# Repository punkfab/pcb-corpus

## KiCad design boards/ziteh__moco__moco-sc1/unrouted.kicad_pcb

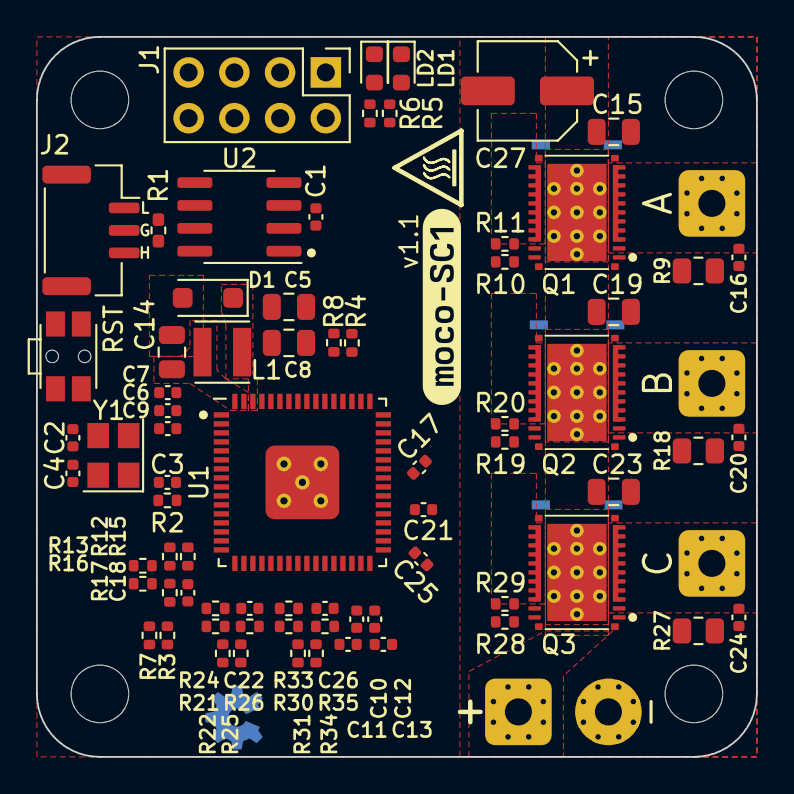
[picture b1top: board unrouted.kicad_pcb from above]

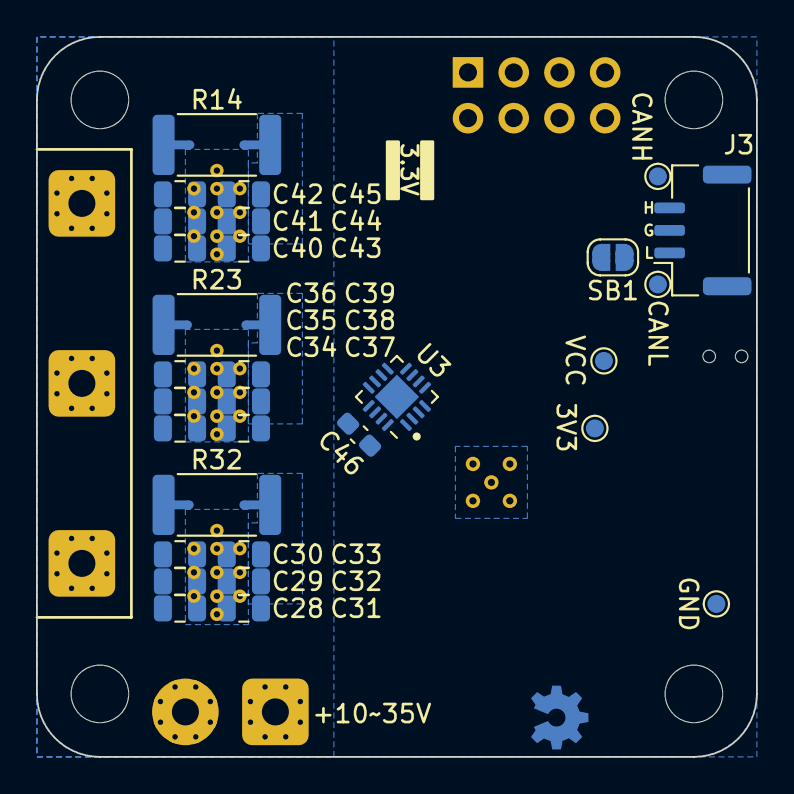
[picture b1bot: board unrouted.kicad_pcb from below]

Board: 4 copper layers, 40.0 x 40.0 mm, 118 parts (36 on the bottom side), 69 nets, no tracks yet.

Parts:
C1, C3, C6, C9, C10, C12: 100nF; C_0402_1005Metric
C2, C4: 6.8pF; C_0402_1005Metric
C5, C28, C29, C30, C31, C32, C33, C34, C35, C36, C37, C38, C39, C40, C41, C42, C43, C44, C45: 10uF/50V; C_0805_2012Metric
C7: 10uF; C_0402_1005Metric
C8, C15, C19, C23: 220nF/50V; C_0805_2012Metric
C11, C13: 1uF; C_0402_1005Metric
C14: 10uF; C_0805_2012Metric
C16, C20, C24: 4.7nF/50V; C_0402_1005Metric
C17, C21, C25: 100nF/50V; C_0402_1005Metric
C18, C22, C26: 1nF; C_0402_1005Metric
C27: 22uF/50V; CP_Elec_5x5.8
C46: 1uF; C_0603_1608Metric_Pad1.08x0.95mm_HandSolder
D1: MBR180S1; D_SOD-123F
H1, H2, H3, H4: MountingHole; MountingHole_3.2mm_M3_ISO14580
J1: Debug; PinHeader_2x04_P2.54mm_Vertical
J2, J3: CAN; JST_GH_SM03B-GHS-TB_1x03-1MP_P1.25mm_Horizontal
J4: V+; wire_rectagnel_3.7mm_D1.5mm
J5: V-; wire_circ_3.7mm_D1.5mm
J6: A; wire_rectagnel_3.7mm_D1.5mm
J7: B; wire_rectagnel_3.7mm_D1.5mm
J8: C; wire_rectagnel_3.7mm_D1.5mm
L1: 18uH; L_Neosid_SMS-ME3015
LD1: Red; LED_0603_1608Metric
LD2: Blue; LED_0603_1608Metric
NT1, NT2, NT3, NT4, NT5, NT6: NetTie_2; NetTie-2_SMD_Pad0.5mm
Q1, Q2, Q3: CSD88584Q5DC; VSON-CLIP-22_5x6mm (DMM0022A)_Alt1
R1: 120R; R_0402_1005Metric_Pad0.72x0.64mm_HandSolder
R2, R6, R7, R8: 10k; R_0402_1005Metric
R3: 100k; R_0402_1005Metric
R4: 22k; R_0402_1005Metric
R5: 1k; R_0402_1005Metric
R9, R18, R27: 2.2R/125mW; R_0805_2012Metric
R10, R11, R19, R20, R28, R29: 10R; R_0402_1005Metric
R12, R15, R21, R24, R30, R33: 24k; R_0402_1005Metric
R13, R16, R22, R25, R31, R34: 1.78k; R_0402_1005Metric
R14, R23, R32: 20mΩ/3W; R_2512_6332Metric
R17, R26, R35: 12k; R_0402_1005Metric
SB1: SolderJumper_2_Open; SolderJumper-2_P1.3mm_Open_RoundedPad1.0x1.5mm
SW1: RESET; SW_SPST_EVQP7C
TP1: CANH; TestPoint_Pad_D1.0mm
TP2: CANL; TestPoint_Pad_D1.0mm
TP3: 3.3V; TestPoint_Pad_D1.0mm
TP4: VCC; TestPoint_Pad_D1.0mm
TP5: GND; TestPoint_Pad_D1.0mm
U1: STSPIN32G4; VFQFPN 9X9X1.0 64 PITCH 0.5
U2: TCAN337; SOIC-8_3.9x4.9mm_P1.27mm
U3: MA702; QFN-16-1EP_3x3mm_P0.5mm_EP1.75x1.75mm
Y1: 16MHz; Crystal_SMD_3225-4Pin_3.2x2.5mm
kibuzzard-64C58EFF: G***; kibuzzard-64C58EFF

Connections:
+3.3V: C1.2, C6.2, C7.2, C9.2, C10.2, C11.2, C12.2, C13.2, C46.2, J1.1, R2.2, R4.1, R12.1, R21.1, R30.1, TP3.1, U1.1 (REG3V3/VDD), U1.2 (VBAT), U1.26 (VREF+), U1.27 (VDDA), U2.3 (VCC), U3.13 (VDD)
/CANH: J2.3, J3.3, SB1.1 (A), TP1.1, U2.7 (CANH)
/CANL: J2.1, J3.1, R1.2, TP2.1, U2.6 (CANL)
/CAN_RX: U1.47 (PA11), U2.4 (RXD)
/CAN_TX: U1.48 (PA12), U2.1 (TXD)
/OPAMP1_VINM: C18.2, R16.2, R17.1, U1.16 (PA3)
/OPAMP1_VINP: R12.2, R13.2, R15.1, U1.14 (PA1)
/OPAMP1_VOUT: C18.1, R17.2, U1.15 (PA2)
/OPAMP2_VINM: C22.2, R25.2, R26.1, U1.22 (PC5)
/OPAMP2_VINP: R21.2, R22.2, R24.1, U1.20 (PA7)
/OPAMP2_VOUT: C22.1, R26.2, U1.19 (PA6)
/OPAMP3_VINM: C26.2, R34.2, R35.1, U1.25 (PB2)
/OPAMP3_VINP: R30.2, R31.2, R33.1, U1.23 (PB0)
/OPAMP3_VOUT: C26.1, R35.2, U1.24 (PB1)
/OSC_IN: C2.2, U1.6 (PF0), Y1.3
/OSC_OUT: C4.2, U1.7 (PF1), Y1.1
/Power Stage/OUTA: C16.1, J6.1, Q1.3 (VSW), Q1.4 (VSW), Q1.5 (VSW), Q1.6 (VSW), Q1.7 (VSW), Q1.8 (VSW), Q1.9 (VSW), Q1.10 (VSW), Q1.11 (VSW)
/Power Stage/OUTB: C20.1, J7.1, Q2.3 (VSW), Q2.4 (VSW), Q2.5 (VSW), Q2.6 (VSW), Q2.7 (VSW), Q2.8 (VSW), Q2.9 (VSW), Q2.10 (VSW), Q2.11 (VSW)
/Power Stage/OUTC: C24.1, J8.1, Q3.3 (VSW), Q3.4 (VSW), Q3.5 (VSW), Q3.6 (VSW), Q3.7 (VSW), Q3.8 (VSW), Q3.9 (VSW), Q3.10 (VSW), Q3.11 (VSW)
/Power Stage/RSA+: NT1.1, R13.1
/Power Stage/RSA-: NT2.1, R16.1
/Power Stage/RSB+: NT3.1, R22.1
/Power Stage/RSB-: NT4.1, R25.1
/Power Stage/RSC+: NT5.1, R31.1
/Power Stage/RSC-: NT6.1, R34.1
/Power Stage/S2A: NT1.2, Q1.12 (PGND), Q1.13 (PGND), Q1.14 (PGND), Q1.15 (PGND), Q1.16 (PGND), Q1.17 (PGND), Q1.18 (PGND), Q1.19 (PGND), Q1.20 (PGND), R14.1
/Power Stage/S2B: NT3.2, Q2.12 (PGND), Q2.13 (PGND), Q2.14 (PGND), Q2.15 (PGND), Q2.16 (PGND), Q2.17 (PGND), Q2.18 (PGND), Q2.19 (PGND), Q2.20 (PGND), R23.1
/Power Stage/S2C: NT5.2, Q3.12 (PGND), Q3.13 (PGND), Q3.14 (PGND), Q3.15 (PGND), Q3.16 (PGND), Q3.17 (PGND), Q3.18 (PGND), Q3.19 (PGND), Q3.20 (PGND), R32.1
/SCREF: R4.2, R8.1, U1.52 (SCREF)
/SPI_MISO: U1.55 (PB4), U3.7 (MISO)
/SPI_MOSI: U1.56 (PB5), U3.4 (MOSI)
/SPI_SCLK: U1.54 (PB3), U3.12 (SCLK)
/SPI_~CS_RS: U1.57 (PB6), U3.5 (~CS)
/SWCLK: J1.5, U1.50 (PA14)
/SWDIO: J1.3, U1.49 (PA13)
/SWO: J1.7, U1.51 (PA15)
/USART_RX: J1.6, U1.46 (PA10)
/USART_TX: J1.4, U1.45 (PA9)
/USER_LED: R5.1, U1.13 (PA0)
/V_{BUS}_SENSE: R3.1, R7.2, U1.17 (PA4)
/~RESET: C3.1, R2.1, SW1.1, U1.8 (PG10)
GND: C1.1, C2.1, C3.2, C4.1, C5.2, C6.1, C7.1, C8.2, C9.1, C10.1, C11.1, C12.1, C13.1, C14.2, C15.1, C19.1, C23.1, C27.2, C28.2, C29.2, C30.2, C31.2, C32.2, C33.2, C34.2, C35.2, C36.2, C37.2, C38.2, C39.2, C40.2, C41.2, C42.2, C43.2, C44.2, C45.2, C46.1, D1.2 (A), J1.2, J1.8, J2.2, J3.2, J5.1, LD1.1 (K), LD2.1 (K), NT2.2, NT4.2, NT6.2, R7.1, R8.2, R9.2, R14.2, R15.2, R18.2, R23.2, R24.2, R27.2, R32.2, R33.2, SW1.2, TP5.1, U1.32 (PGND), U1.59 (PB8), U1.65 (VSS), U2.2 (GND), U3.8 (GND), U3.10 (TEST), U3.17 (PAD), Y1.2, Y1.4
unnamed: C16.2, R9.1
unnamed: C20.2, R18.1
unnamed: C24.2, R27.1
unnamed: D1.1 (K), L1.1, U1.62 (SW)
unnamed: LD1.2 (A), R5.2
unnamed: LD2.2 (A), R6.2
unnamed: Q1.1 (GH), R10.2
unnamed: Q1.22 (GL), R11.2
unnamed: C17.1, Q1.2 (SH), U1.42 (OUT1)
unnamed: Q2.1 (GH), R19.2
unnamed: Q2.22 (GL), R20.2
unnamed: C21.1, Q2.2 (SH), U1.39 (OUT2)
unnamed: Q3.1 (GH), R28.2
unnamed: Q3.22 (GL), R29.2
unnamed: C25.1, Q3.2 (SH), U1.36 (OUT3)
unnamed: R1.1, SB1.2 (B)
unnamed: C17.2, U1.41 (BOOT1)
unnamed: R10.1, U1.43 (GHS1)
unnamed: R11.1, U1.29 (GLS1)
unnamed: C21.2, U1.38 (BOOT2)
unnamed: R19.1, U1.40 (GHS2)
unnamed: R20.1, U1.30 (GLS2)
unnamed: C25.2, U1.35 (BOOT3)
unnamed: R28.1, U1.37 (GHS3)
unnamed: R29.1, U1.31 (GLS3)
VBUS: C5.1, C8.1, C15.2, C19.2, C23.2, C27.1, C28.1, C29.1, C30.1, C31.1, C32.1, C33.1, C34.1, C35.1, C36.1, C37.1, C38.1, C39.1, C40.1, C41.1, C42.1, C43.1, C44.1, C45.1, J4.1, Q1.27 (VIN), Q2.27 (VIN), Q3.27 (VIN), R3.2, U1.61 (VM)
VCC: C14.1, L1.2, R6.1, TP4.1, U1.63 (VCC), U1.64 (REGIN)

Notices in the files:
boards/ziteh__moco__moco-sc1/unrouted.kicad_pcb:
Open source hardware, CERN-OHL-P v2
